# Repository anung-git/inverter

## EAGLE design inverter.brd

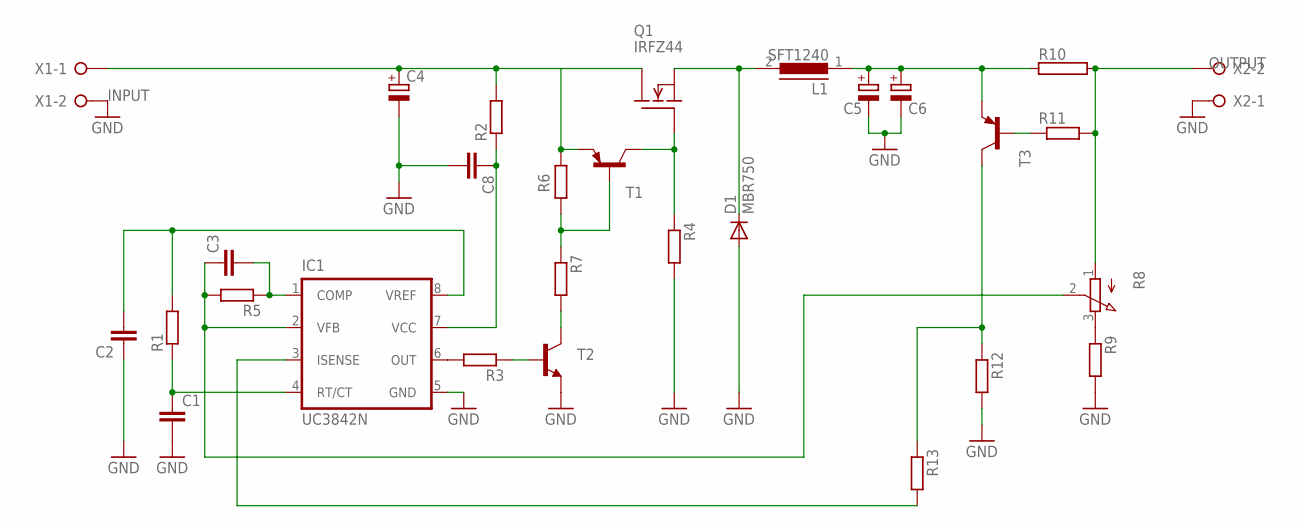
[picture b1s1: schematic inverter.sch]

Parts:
C1, C3: C-EU050-024X044; C050-024X044
C2, C8: C-EU050-025X075; C050-025X075
C4, C5, C6: CPOL-EUE5-8.5; E5-8,5
D1: MBR750; TO220AC
IC1: UC3842N; DIL08
L1: SFT1240
Q1: IRFZ44; TO220
R1, R2, R3, R4, R5, R6, R7, R9, R11, R12, R13: R-EU_0207/10; 0207/10
R8: 3RP/1610N
R10: RKH208-8; KH208-8
T1, T3: BC557A-PNP-TO92-EBC; TO92-EBC
T2: BC547-NPN-TO92-CBE; TO92-CBE
X1, X2: W237-02P; W237-132

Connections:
GND: C1.2, C2.1, C4.-, C5.-, C6.-, C8.2, D1.A, IC1.5 (GND), R4.2, R9.2, R12.2, T2.E, X1.2, X2.1
unnamed: IC1.6 (OUT), R3.2
unnamed: Q1.1 (G), R4.1, T1.C
unnamed: D1.C, L1.2, Q1.3 (S)
unnamed: C2.2, IC1.8 (VREF), R1.2
unnamed: C1.1, IC1.4 (RT/CT), R1.1
unnamed: C3.1, IC1.2 (VFB), R5.2, R8.2 (S)
unnamed: C3.2, IC1.1 (COMP), R5.1
unnamed: C8.1, IC1.7 (VCC), R2.1
unnamed: C4.+, Q1.2 (D), R2.2, R6.1, T1.E, X1.1
unnamed: R3.1, T2.B
unnamed: R7.2, T2.C
unnamed: R6.2, R7.1, T1.B
unnamed: R8.1 (A), R10.2, R11.2, X2.2
unnamed: R8.3 (E), R9.1
unnamed: C5.+, C6.+, L1.1, R10.1, T3.E
unnamed: R11.1, T3.B
unnamed: IC1.3 (ISENSE), R13.2
unnamed: R12.1, R13.1, T3.C

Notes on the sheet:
OUTPUT
INPUT

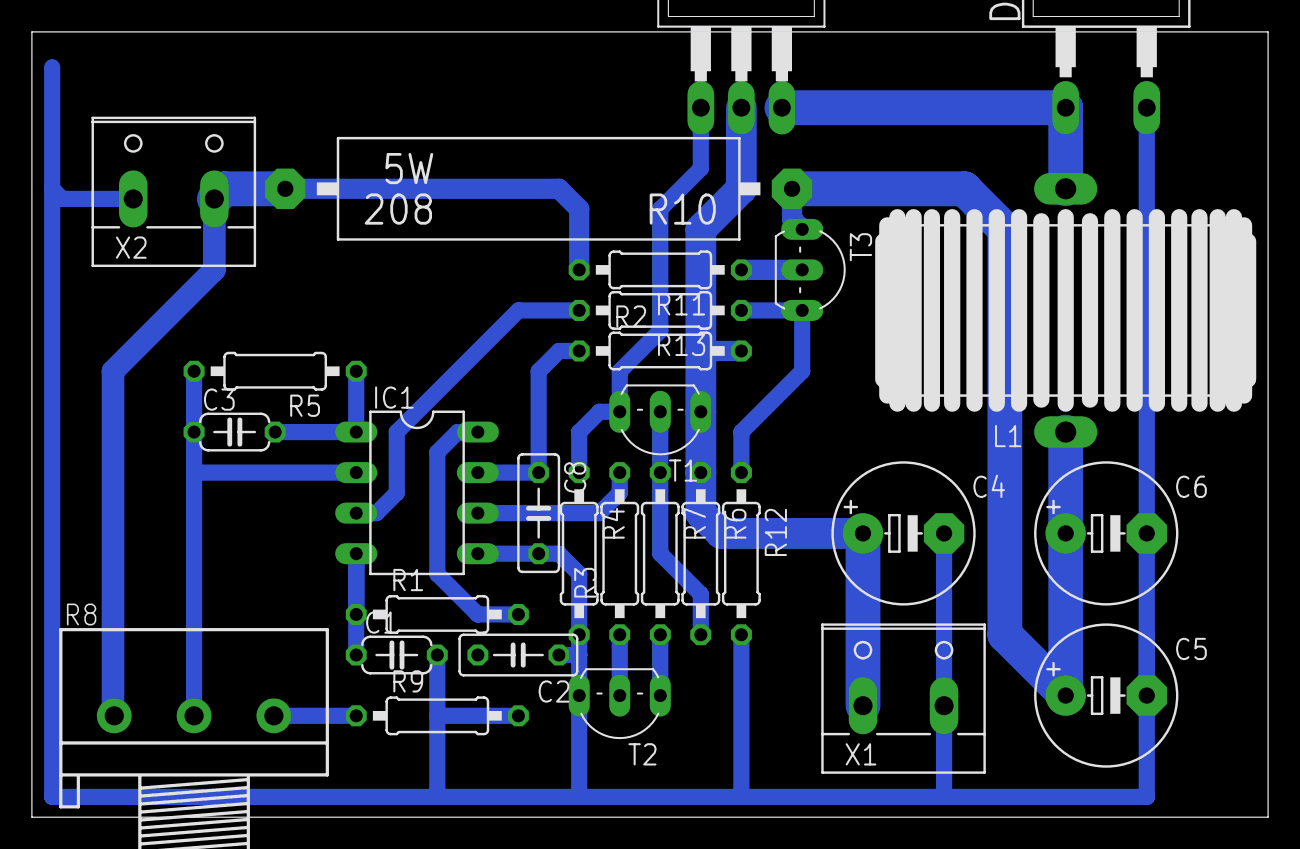
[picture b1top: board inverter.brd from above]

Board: 2 copper layers, 77.5 x 49.2 mm, 29 parts (0 on the bottom side), 19 nets.

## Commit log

2019-09-15 upload file pcb
2019-09-15 gambar
